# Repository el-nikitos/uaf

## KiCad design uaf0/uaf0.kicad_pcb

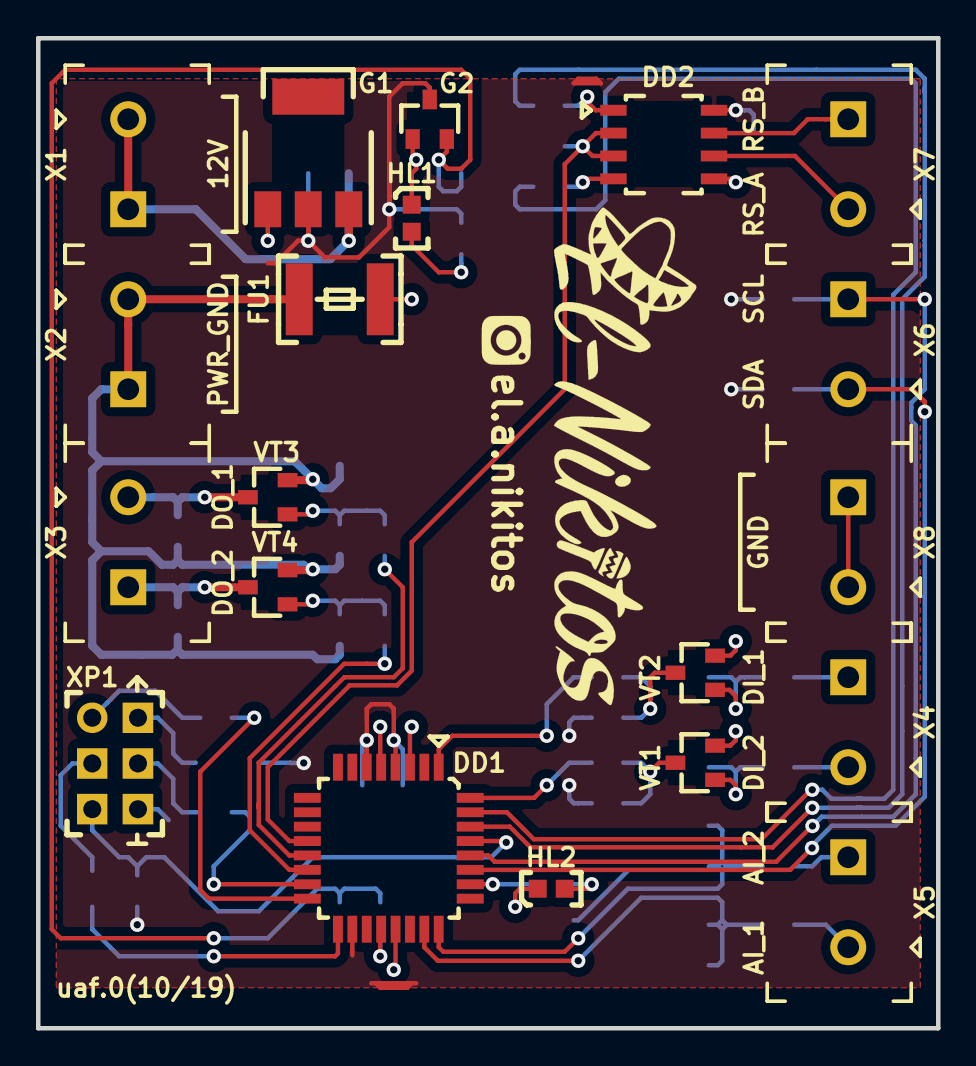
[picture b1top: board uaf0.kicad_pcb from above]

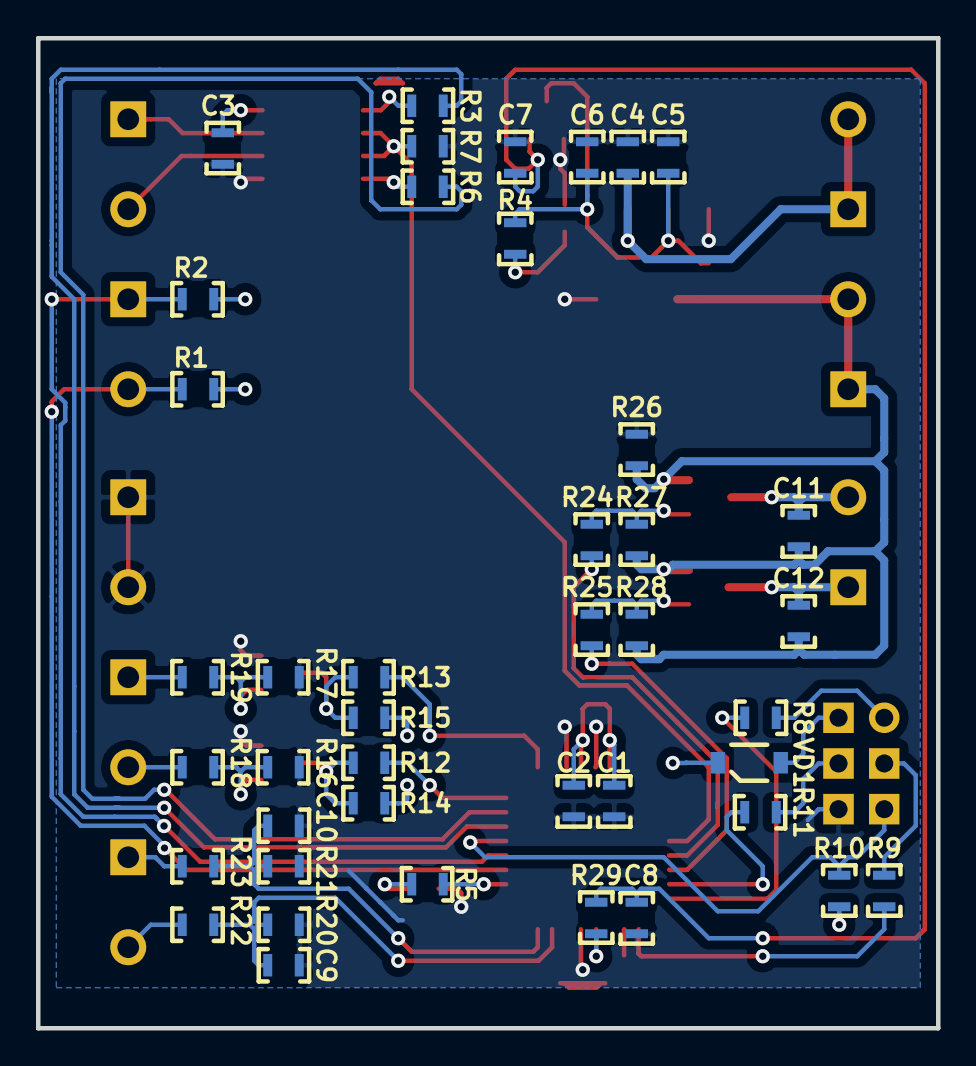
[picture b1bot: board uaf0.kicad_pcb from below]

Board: 2 copper layers, 50.0 x 55.0 mm, 62 parts (42 on the bottom side), 44 nets.

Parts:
C1, C2, C3, C4, C5, C6, C7, C8, C9, C10, C11, C12: Конденсатор_керамический; Конденсатор_SMD_0603
DD1: ATmega8A-AU; микросхема_ATMEGA-8-161AU
DD2: 5559ИН10_28(UART-RS485); SO-8
FU1: Предохранитель_0.1A; Предохранитель_SMD_1812
G1: стабилизатор_нерегулируемый_LM1117GS-5.0; Транзистор_NPN_SOT223
G2: стабилизатор_нерегулируемый_XC6206P302MR; Транзистор_IRLML6344TR_SOT-23
HL1, HL2: Светодиод; Светодиод_SMD_0603
R1, R2, R3, R4, R5, R6, R7, R8, R9, R10, R11, R12, R13, R14, R15, R16, R17, R18, R19, R20, R21, R22, R23, R24, R25, R26, R27, R28, R29: Резистор_0,065Вт; Резистор_SMD_0603_0,065_Вт
VD1: Диод_шоттки_S13; Диод_S13_SOD-123
VT1, VT2, VT3, VT4: Транзистор_полевой_N-IRLML6344TR; Транзистор_IRLML6344TR_SOT-23
X1, X2, X3, X4, X5, X6, X7, X8: Клеммник_х2; Клеммник_х2_шаг5
XP1: Вилка_PLD6_ПРОГ; Вилка_PLD6_вертикальная

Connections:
/3V: C7.1, C8.1, G2.2, R29.2
/5V: C1.1, C2.1, C3.2, C5.1, C6.1, DD1.4, DD1.6, DD1.18, DD2.8, G1.2, G2.3, R1.1, R2.1, R4.1, R10.1, R14.1, R15.1, VD1.2
/12V: C4.1, G1.3, X1.1, X1.2
/AI_1: R22.2, X5.1
/AI_2: R23.2, X5.2
/DI_1: R19.2, X4.2
/DI_2: R18.2, X4.1
/DO_1: C11.1, VT3.3, X3.1
/DO_2: C12.1, VT4.3, X3.2
/GND: C1.2, C2.2, C3.1, C4.2, C5.2, C6.2, C7.2, C8.2, C9.2, C10.2, DD1.3, DD1.5, DD1.21, DD2.5, FU1.2, G1.1, G2.1, HL1.2, HL2.2, R7.2, R16.1, R17.1, R20.2, R21.2, R26.2, VT1.2, VT2.2, X8.1, X8.2, XP1.6
/MISO: DD1.16, R8.1
/MOSI: DD1.15, R11.2
/PB0: DD1.12, DD2.2, DD2.3, R7.1
/PB1_OC1A: DD1.13, R24.1
/PB2_OC1B: DD1.14, R25.1
/PC0: C9.1, DD1.23, R20.1, R22.1
/PC1: C10.1, DD1.24, R21.1, R23.1
/PC3: DD1.26, R5.1
/PD2_INT0: DD1.32, R12.1
/PD3_INT1: DD1.1, R13.1
/PWR_GND: C11.2, C12.2, FU1.1, R26.1, R27.1, R28.1, VT3.2, VT4.2, X2.1, X2.2
/RES: DD1.29, R10.2, XP1.5
/RS485_A: DD2.6, X7.1
/RS485_B: DD2.7, X7.2
/RX: DD1.30, R3.2
/SCK: DD1.17, R9.1
/SCL: DD1.28, R2.2, X6.2
/SDA: DD1.27, R1.2, X6.1
/TX: DD1.31, R6.2
/VCC_PROG: VD1.1, XP1.2
unnamed: DD1.20, R29.1
unnamed: DD2.1, R3.1
unnamed: DD2.4, R6.1
unnamed: HL1.1, R4.2
unnamed: HL2.1, R5.2
unnamed: R8.2, XP1.1
unnamed: R9.2, XP1.3
unnamed: R11.1, XP1.4
unnamed: R12.2, R14.2, VT1.3
unnamed: R13.2, R15.2, VT2.3
unnamed: R16.2, R18.1, VT1.1
unnamed: R17.2, R19.1, VT2.1
unnamed: R24.2, R27.2, VT3.1
unnamed: R25.2, R28.2, VT4.1

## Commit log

2019-10-19 инициализирован проект, начата схема
2019-10-19 схема+трассировка, требуется проверка
    не установлена ссылка на инстаграм
2019-10-20 исправлена шелкография, добавлены файлы производства v0
2019-10-30 добавлена PDF схемы
2019-11-03 откорректирована схема+добавлен тестовый скетч
2021-04-07 скетч для генератора "колоколов"
